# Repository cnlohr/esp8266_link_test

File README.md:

#ESP8266/ESP8285 Range Test Tool

Simply say make server_burn or make client_burn.

This will make a client or a server ESP.  The SSID is "rangetest" password is "soldering."

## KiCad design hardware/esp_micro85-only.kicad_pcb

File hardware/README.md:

In here is the kicad project files for a board that uses a ESP-12-(E/F) module as well as a raw ESP8285.

The .pngs are: 600dpi for the ESP-12-E board and 1200 dpi for the ESP8285 board.  The PNGs have this encoded in them, so should be drag-and-drop to OpenOffice Writer or anything like that.

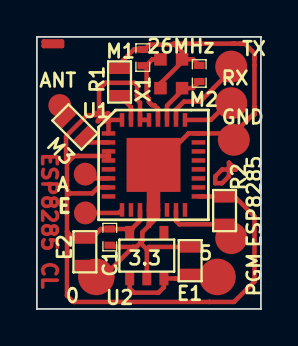
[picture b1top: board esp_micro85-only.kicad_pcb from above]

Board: 2 copper layers, 12.4 x 15.1 mm, 20 parts (0 on the bottom side), 13 nets.

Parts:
C1: .1u; SM0402
E1, E2: 10u; SM0603
M1, M2: 5.6p; SM0402
M3: 5.6p; SM0603
P1: RX; .1SMTPIN
P2: TX; .1SMTPIN
P3: GND; .1SMTPIN
P4: ANT; .1SMTPIN
P5: A; .1SMTPIN
P6: 0; .1SMTPIN
P7: 5; .1SMTPIN
P8: PGM; .1SMTPIN
P9: E; .1SMTPIN
R1, R2: 12k; SM0603
U1: ESP8285; QFN32
U2: 3.3; SOT23-5
X1: 26MHz; XTAL4TINY

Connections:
+3.3V: C1.2, E2.2, R2.1, U1.1, U1.3, U1.4, U1.7, U1.11, U1.17, U1.29, U1.30, U1.32, U2.5
+5V: E1.2, P7.1, U2.1, U2.3
GND: C1.1, E1.1, E2.1, M1.2, M2.2, P3.1, P6.1, R1.1, U1.12, U1.13, U1.24, U1.33, U2.2, X1.3, X1.4
unnamed: P5.1, U1.6
unnamed: P2.1, U1.26
unnamed: P1.1, U1.25
unnamed: P8.1, R2.2, U1.15
unnamed: P9.1, U1.9
unnamed: M1.1, U1.28, X1.1
unnamed: M3.2, U1.2
unnamed: M2.1, U1.27, X1.2
unnamed: R1.2, U1.31
unnamed: M3.1, P4.1

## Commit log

2016-06-29 Yay! link test working.
2016-07-03 update server/client
2016-07-07 add example files
2016-07-07 update hardware
